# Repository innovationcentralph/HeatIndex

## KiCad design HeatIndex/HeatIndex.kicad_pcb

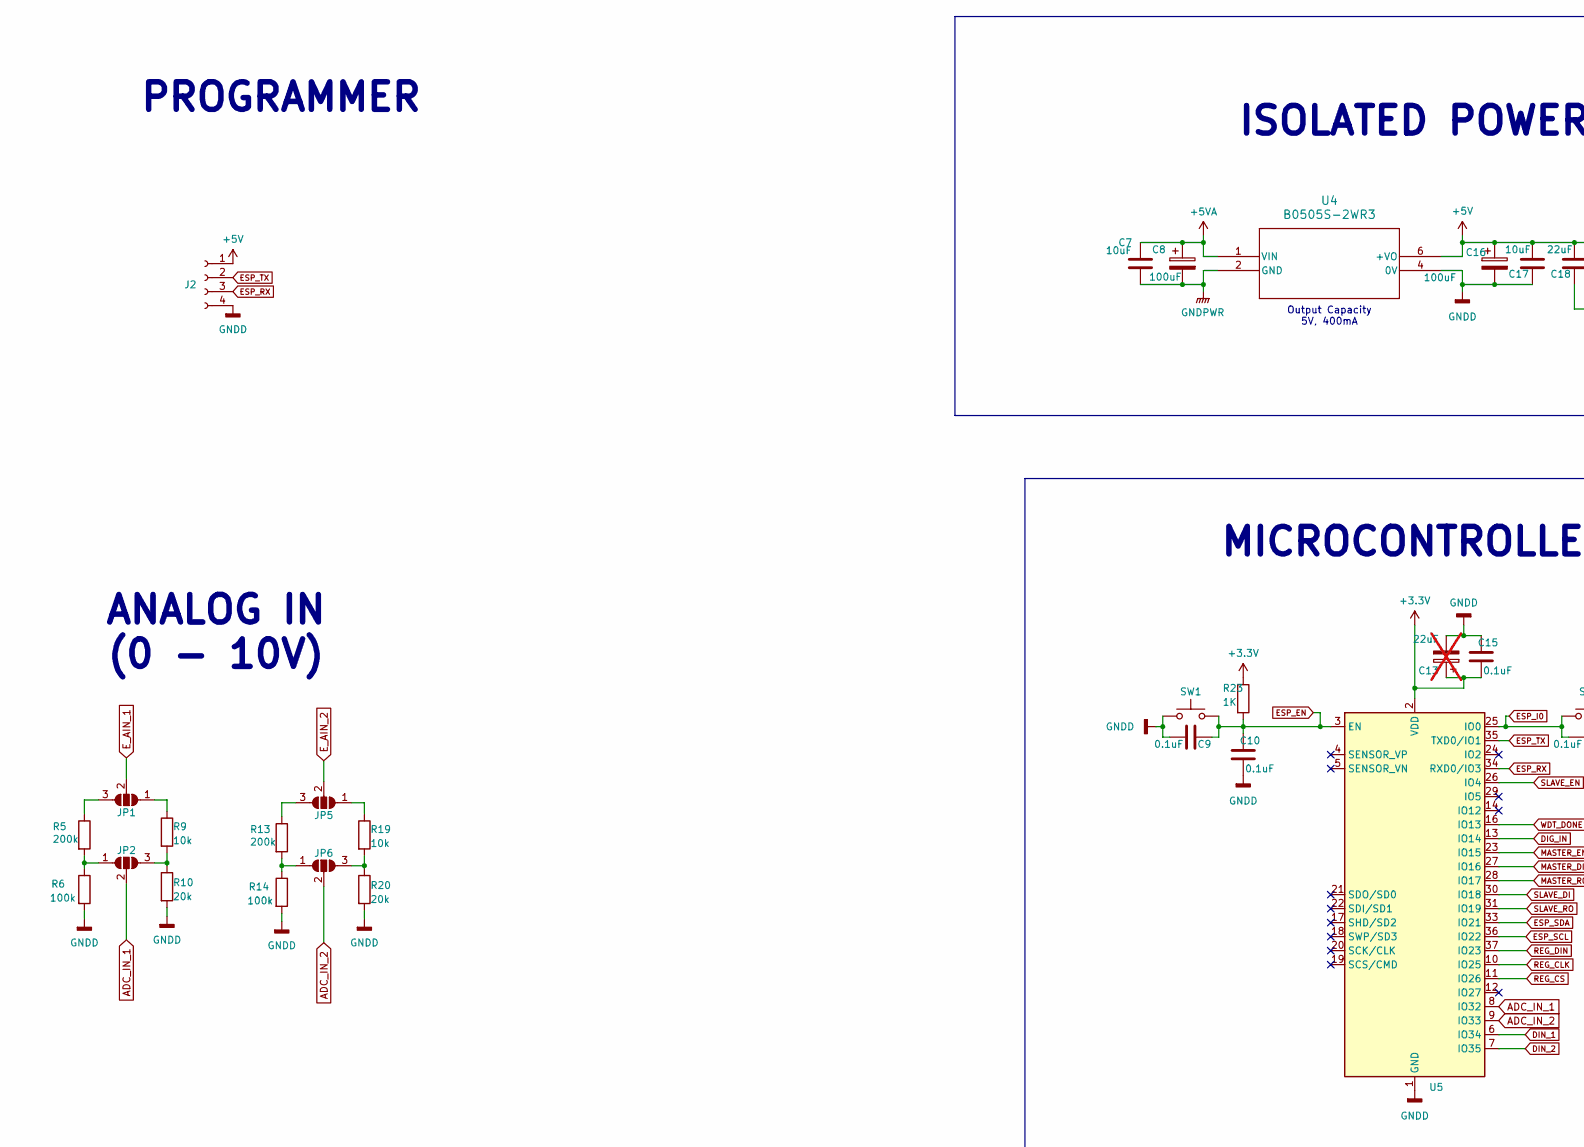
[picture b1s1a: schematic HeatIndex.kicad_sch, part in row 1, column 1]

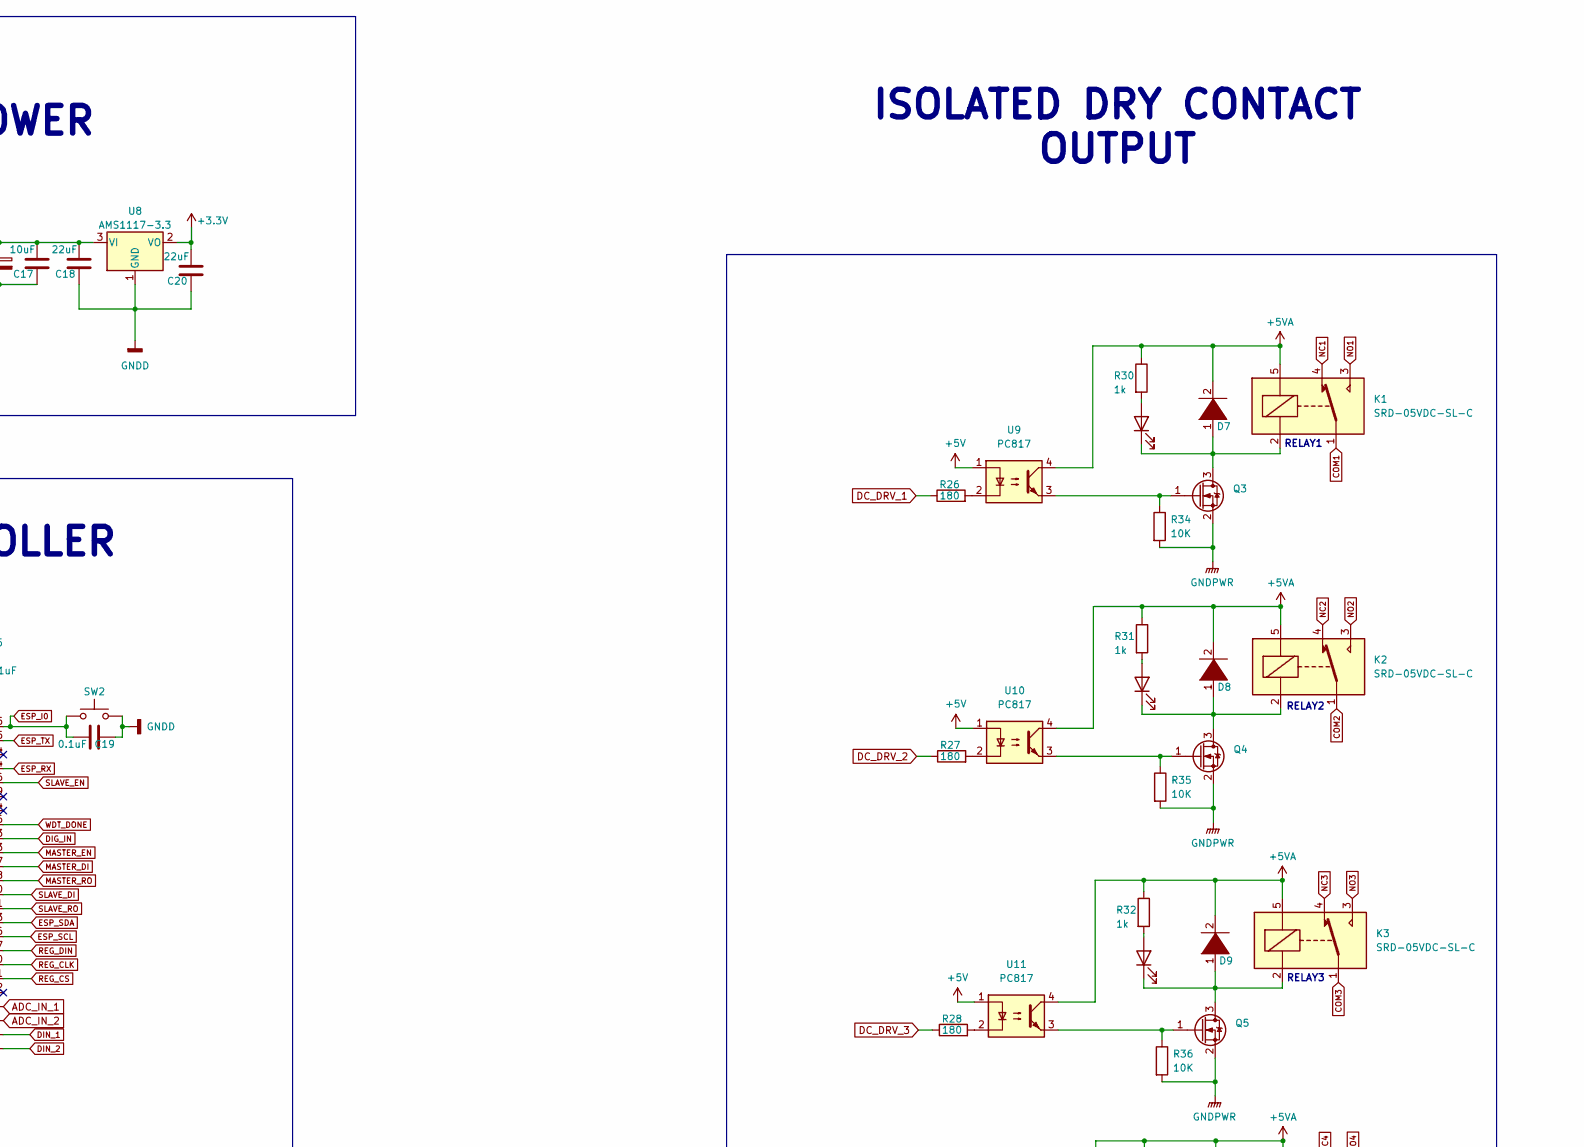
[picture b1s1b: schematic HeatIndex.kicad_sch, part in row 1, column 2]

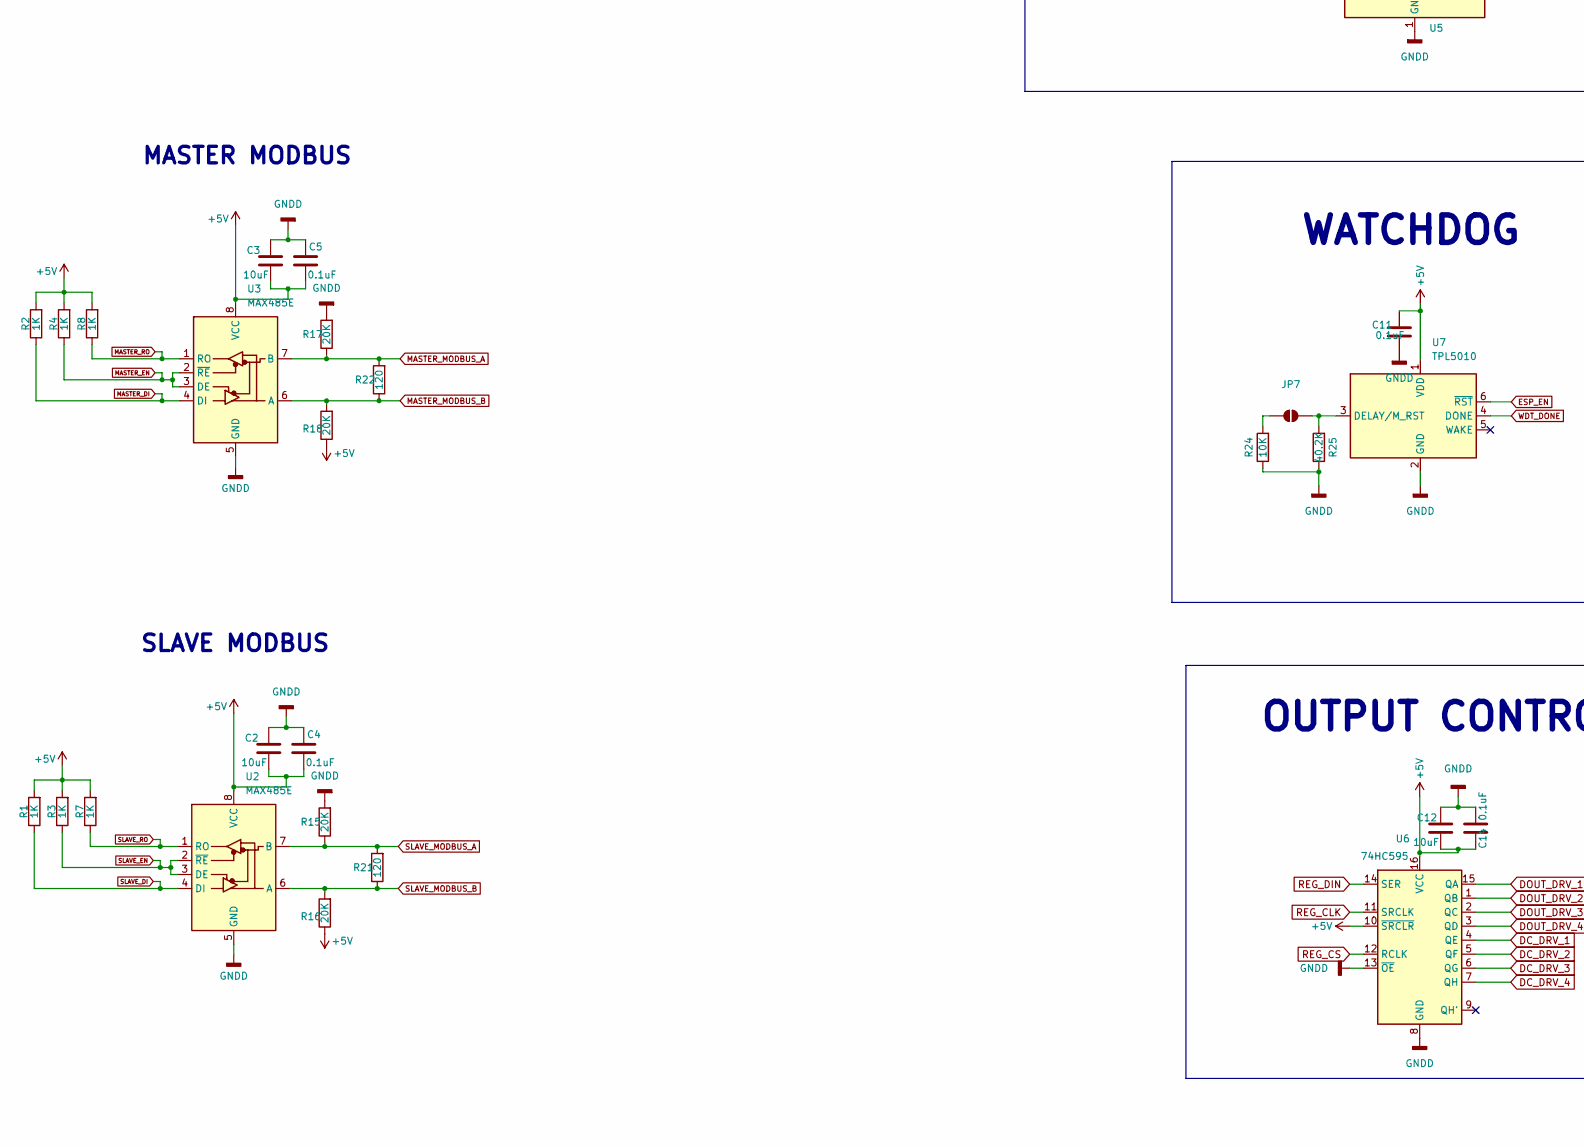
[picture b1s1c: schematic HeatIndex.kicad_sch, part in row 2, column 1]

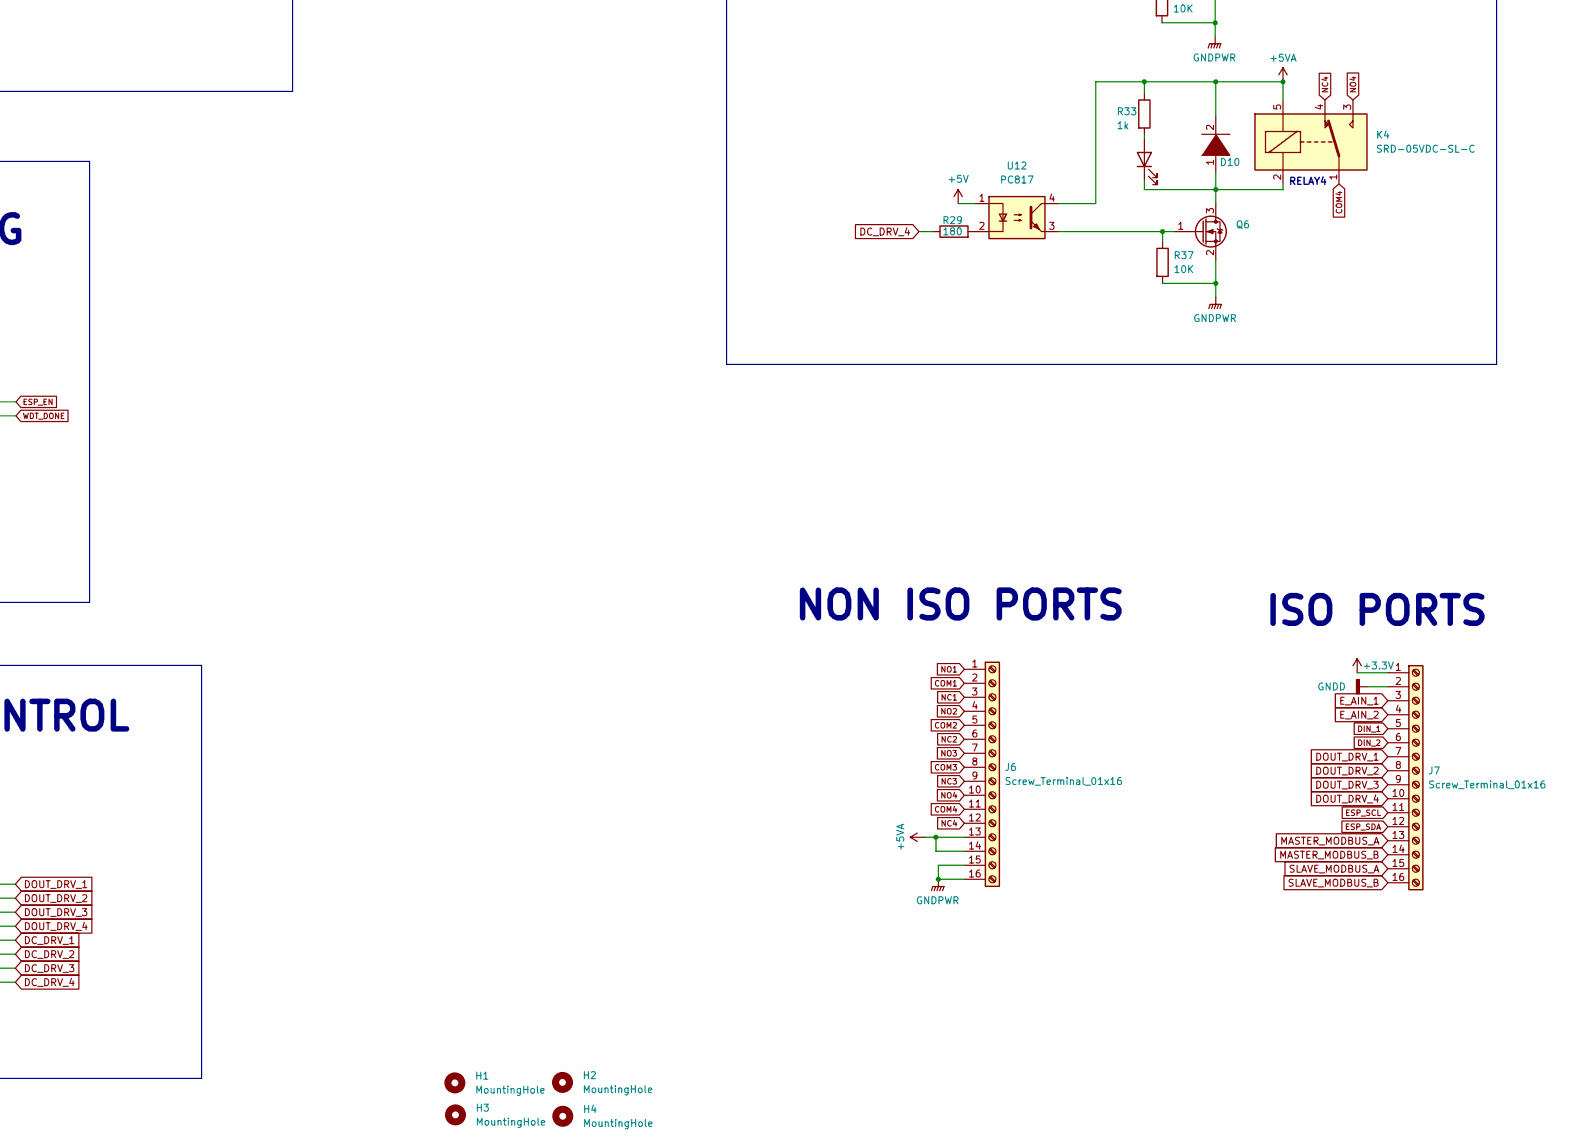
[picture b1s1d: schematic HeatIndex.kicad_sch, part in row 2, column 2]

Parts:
C2, C3, C7, C12, C17: 10uF; C_0805_2012Metric_Pad1.18x1.45mm_HandSolder; LCSC C15850
C4, C5, C9, C10, C11, C14, C15, C19: 0.1uF; C_0603_1608Metric; LCSC C80516
C8, C16: 100uF; C_1210_3225Metric_Pad1.33x2.70mm_HandSolder; LCSC C394395
C13: 22uF; C_0603_1608Metric; LCSC C59461; not fitted
C18, C20: 22uF; C_0603_1608Metric; LCSC C59461
D3, D4, D5, D6: LED; LED_0805_2012Metric_Pad1.15x1.40mm_HandSolder; LCSC C2297
D7, D8, D9, D10: 1N4001; D_SOD-123F; LCSC C2892326
H1, H2, H3, H4: MountingHole; MountingHole_3.2mm_M3_DIN965_Pad_TopBottom
J2: Conn_01x04_Socket; JST_EH_B4B-EH-A_1x04_P2.50mm_Vertical
J6, J7: Screw_Terminal_01x16; TerminalBlock_Phoenix_MKDS-1,5-16-5.08_1x16_P5.08mm_Horizon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
JP1, JP2, JP5, JP6: SolderJumper_3_Open; SolderJumper-3_P1.3mm_Open_Pad1.0x1.5mm
JP7: SolderJumper_2_Open; SolderJumper-2_P1.3mm_Open_Pad1.0x1.5mm
K1, K2, K3, K4: SRD-05VDC-SL-C; Relay_SPDT_SANYOU_SRD_Series_Form_C; LCSC C35449
Q3, Q4, Q5, Q6: Q_NMOS_Depletion_GSD; SOT-23-3; LCSC C75882
R1, R2, R3, R4, R7, R8, R23: 1K; R_0603_1608Metric_Pad0.98x0.95mm_HandSolder; LCSC C21190
R5, R13: 200k; R_0603_1608Metric_Pad0.98x0.95mm_HandSolder; LCSC C95331
R6, R14: 100k; R_0603_1608Metric_Pad0.98x0.95mm_HandSolder; LCSC C14675
R9, R19: 10k; R_0603_1608Metric_Pad0.98x0.95mm_HandSolder; LCSC C25804
R10, R20: 20k; R_0603_1608Metric_Pad0.98x0.95mm_HandSolder; LCSC C2907011
R15, R16, R17, R18: 20K; R_0805_2012Metric_Pad1.20x1.40mm_HandSolder; LCSC C4328
R21, R22: 120; R_0805_2012Metric_Pad1.20x1.40mm_HandSolder; LCSC C114245
R24, R34, R35, R36, R37: 10K; R_0603_1608Metric_Pad0.98x0.95mm_HandSolder; LCSC C25804
R25: 40.2K; R_0603_1608Metric_Pad0.98x0.95mm_HandSolder; LCSC C12447
R26, R27, R28, R29: 180; R_0603_1608Metric_Pad0.98x0.95mm_HandSolder; LCSC C25210
R30, R31, R32, R33: 1k; R_0603_1608Metric_Pad0.98x0.95mm_HandSolder; LCSC C21190
SW1, SW2: SW_Push; SW_SPST_CK_RS282G05A3; LCSC C2689642
U2, U3: MAX485E; SOP-8_3.9x4.9mm_P1.27mm; LCSC C481667
U4: B0505S-2WR3; B_S-2WR2_MNS; LCSC C5369473
U5: ESP32-WROOM-32; LCSC C529577
U6: 74HC595; SOIC-16_3.9x9.9mm_P1.27mm; LCSC C5947
U7: TPL5010; SOT-23-6; LCSC C473912
U8: AMS1117-3.3; SOT-223-3_TabPin2; LCSC C6186
U9, U10, U11, U12: PC817; APC-817xx-SL_AMB; LCSC C66405

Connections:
+3.3V: C13.1, C15.1, C20.2, J7.1, R23.1, U5.2 (VDD), U8.2 (VO)
+5V: C2.2, C3.2, C4.1, C5.1, C11.1, C12.2, C14.2, C16.1, C17.2, C18.2, J2.1, R1.2, R2.2, R3.2, R4.2, R7.2, R8.2, R16.1, R18.1, U2.8 (VCC), U3.8 (VCC), U4.6 (+VO), U6.10 (~SRCLR), U6.16 (VCC), U7.1 (VDD), U8.3 (VI), U9.1, U10.1, U11.1, U12.1
+5VA: C7.2, C8.1, D7.2 (A), D8.2 (A), D9.2 (A), D10.2 (A), J6.13, J6.14, K1.5, K2.5, K3.5, K4.5, R30.1, R31.1, R32.1, R33.1, U4.1 (VIN), U9.4, U10.4, U11.4, U12.4
ADC_IN_1: JP2.2 (C), U5.8 (IO32)
ADC_IN_2: JP6.2 (C), U5.9 (IO33)
COM1: J6.2, K1.1
COM2: J6.5, K2.1
COM3: J6.8, K3.1
COM4: J6.11, K4.1
DC_DRV_1: R26.1, U6.4 (QE)
DC_DRV_2: R27.1, U6.5 (QF)
DC_DRV_3: R28.1, U6.6 (QG)
DC_DRV_4: R29.1, U6.7 (QH)
DIG_IN: U5.13 (IO14)
DIN_1: J7.5, U5.6 (IO34)
DIN_2: J7.6, U5.7 (IO35)
DOUT_DRV_1: J7.7, U6.15 (QA)
DOUT_DRV_2: J7.8, U6.1 (QB)
DOUT_DRV_3: J7.9, U6.2 (QC)
DOUT_DRV_4: J7.10, U6.3 (QD)
ESP_EN: C9.2, C10.2, R23.2, SW1.2, U5.3 (EN), U7.6 (~RST)
ESP_I0: C19.1, SW2.1, U5.25 (IO0)
ESP_RX: J2.3, U5.34 (RXD0/IO3)
ESP_SCL: J7.11, U5.36 (IO22)
ESP_SDA: J7.12, U5.33 (IO21)
ESP_TX: J2.2, U5.35 (TXD0/IO1)
E_AIN_1: J7.3, JP1.2 (C)
E_AIN_2: J7.4, JP5.2 (C)
GNDD: C2.1, C3.1, C4.2, C5.2, C9.1, C10.1, C11.2, C12.1, C13.2, C14.1, C15.2, C16.2, C17.1, C18.1, C19.2, C20.1, J2.4, J7.2, R6.2, R10.2, R14.2, R15.2, R17.2, R20.2, R24.1, R25.1, SW1.1, SW2.2, U2.5 (GND), U3.5 (GND), U4.4 (0V), U5.1 (GND), U5.15 (GND), U5.38 (GND), U5.39 (GND), U6.8 (GND), U6.13 (~OE), U7.2 (GND), U8.1 (GND)
GNDPWR: C7.1, C8.2, J6.15, J6.16, Q3.2 (S), Q4.2 (S), Q5.2 (S), Q6.2 (S), R34.2, R35.2, R36.2, R37.2, U4.2 (GND)
MASTER_DI: R2.1, U3.4 (DI), U5.27 (IO16)
MASTER_EN: R4.1, U3.2 (~RE), U3.3 (DE), U5.23 (IO15)
MASTER_MODBUS_A: J7.13, R17.1, R22.2, U3.7 (B)
MASTER_MODBUS_B: J7.14, R18.2, R22.1, U3.6 (A)
MASTER_RO: R8.1, U3.1 (RO), U5.28 (IO17)
NC1: J6.3, K1.4
NC2: J6.6, K2.4
NC3: J6.9, K3.4
NC4: J6.12, K4.4
NO1: J6.1, K1.3
NO2: J6.4, K2.3
NO3: J6.7, K3.3
NO4: J6.10, K4.3
unnamed: D3.2 (A), R30.2
unnamed: D3.1 (K), D7.1 (K), K1.2, Q3.3 (D)
unnamed: D4.2 (A), R31.2
unnamed: D4.1 (K), D8.1 (K), K2.2, Q4.3 (D)
unnamed: D5.2 (A), R32.2
unnamed: D5.1 (K), D9.1 (K), K3.2, Q5.3 (D)
unnamed: D6.2 (A), R33.2
unnamed: D6.1 (K), D10.1 (K), K4.2, Q6.3 (D)
unnamed: JP1.1 (A), R9.1
unnamed: JP1.3 (B), R5.1
unnamed: JP2.1 (A), R5.2, R6.1
unnamed: JP2.3 (B), R9.2, R10.1
unnamed: JP5.1 (A), R19.1
unnamed: JP5.3 (B), R13.1
unnamed: JP6.1 (A), R13.2, R14.1
unnamed: JP6.3 (B), R19.2, R20.1
unnamed: JP7.1 (A), R24.2
unnamed: JP7.2 (B), R25.2, U7.3 (DELAY/M_RST)
unnamed: Q3.1 (G), R34.1, U9.3
unnamed: Q4.1 (G), R35.1, U10.3
unnamed: Q5.1 (G), R36.1, U11.3
unnamed: Q6.1 (G), R37.1, U12.3
unnamed: R26.2, U9.2
unnamed: R27.2, U10.2
unnamed: R28.2, U11.2
unnamed: R29.2, U12.2
REG_CLK: U5.10 (IO25), U6.11 (SRCLK)
REG_CS: U5.11 (IO26), U6.12 (RCLK)
REG_DIN: U5.37 (IO23), U6.14 (SER)
SLAVE_DI: R1.1, U2.4 (DI), U5.30 (IO18)
SLAVE_EN: R3.1, U2.2 (~RE), U2.3 (DE), U5.26 (IO4)
SLAVE_MODBUS_A: J7.15, R15.1, R21.2, U2.7 (B)
SLAVE_MODBUS_B: J7.16, R16.2, R21.1, U2.6 (A)
SLAVE_RO: R7.1, U2.1 (RO), U5.31 (IO19)
WDT_DONE: U5.16 (IO13), U7.4 (DONE)

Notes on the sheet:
RELAY1
Output Capacity 5V, 400mA
WATCHDOG
RELAY4
ISOLATED DRY CONTACT OUTPUT
MASTER MODBUS
SLAVE MODBUS
ISOLATED POWER
RELAY3
PROGRAMMER
ISO PORTS
MICROCONTROLLER
NON ISO PORTS
ANALOG IN (0 - 10V)
OUTPUT CONTROL
RELAY2

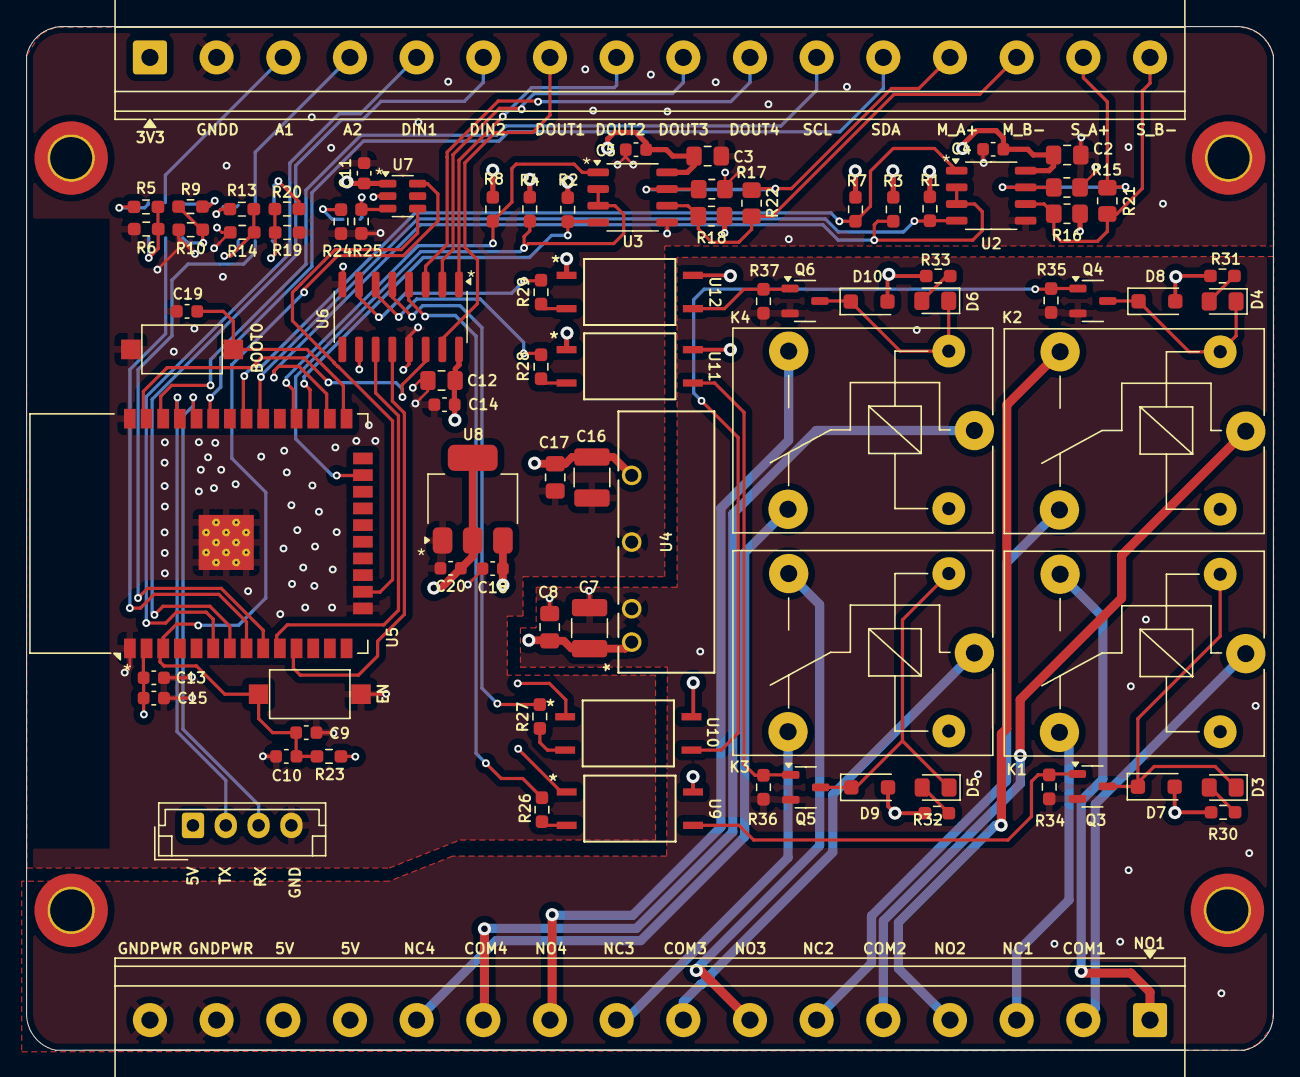
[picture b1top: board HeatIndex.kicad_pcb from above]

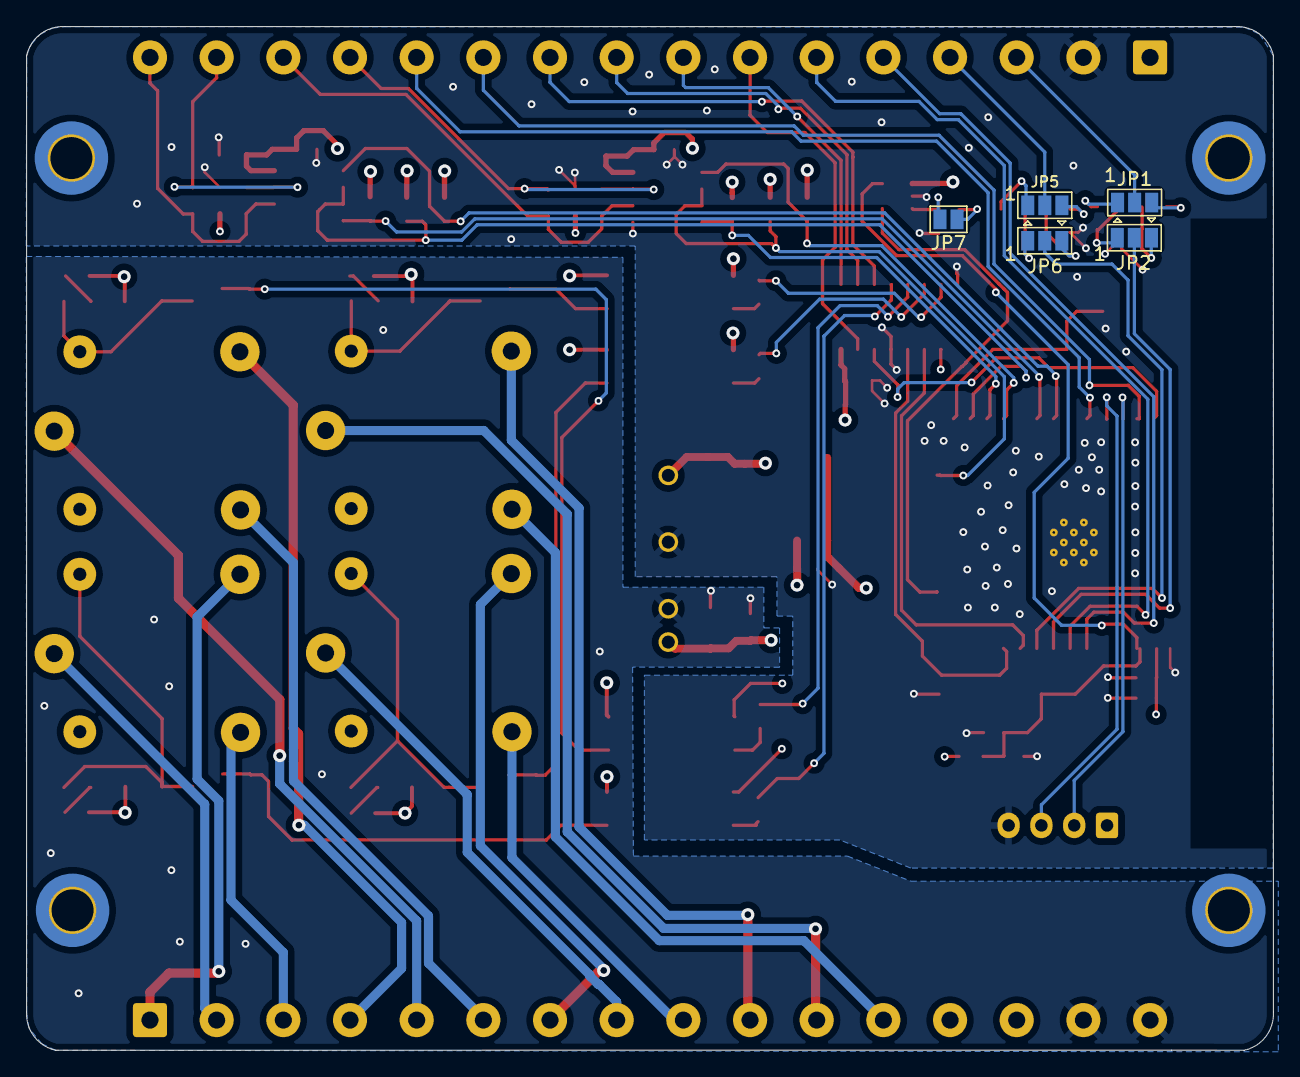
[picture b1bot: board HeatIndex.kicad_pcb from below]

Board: 4 copper layers, 95.0 x 78.0 mm, 94 parts (5 on the bottom side), 77 nets.

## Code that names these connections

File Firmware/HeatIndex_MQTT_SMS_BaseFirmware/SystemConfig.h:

#ifndef SYSTEM_CONFIG_H
#define SYSTEM_CONFIG_H

#include <Arduino.h>
#include "NetworkMqttManager.h"
//==============================================================================
//                              DEBUG FLAGS
//==============================================================================
// Uncomment to enable serial debug output for each subsystem
 #define DEBUG_WIFI
 #define DEBUG_MQTT
 #define DEBUG_SENSOR
 #define DEBUG_TH
 #define DEBUG_CONTACTS
 #define DEBUG_SMS


//==============================================================================
//                               HARDWARE PINS
//==============================================================================


// Master enable / data lines (e.g., for GSM or other radio)
#define MASTER_RO 26  // Master Read Only line
#define MASTER_DI 25  // Master Data In line
#define MASTER_EN 27  // Master Enable line

#define GSM_PWR 4

// LEDs
#define NETWORK_INDICATOR 12     // Server Connectivity LED
#define ACTIVE_INDICATOR 13  // IDLE Indicator LED
#define LED_ON HIGH
#define LED_OFF LOW

//==============================================================================
//                             STRUCTURES
//==============================================================================
typedef struct {
  char mqttServer[64];
  char mqttUser[32];
  char mqttPassword[32];
  int mqttPort;
} MQTTConfig_t;

typedef struct {
  char ssid[32];
  char password[64];
} WiFiCreds_t;

typedef struct{
  int normal;
  int warning;
  int alert;
  int critical;
} Thresholds_t;

typedef struct{
  bool green;
  bool blue;
  bool orange;
  bool red;
} TowerLight_t;

enum TowerLightState {
  STATE_GREEN,
  STATE_BLUE,
  STATE_ORANGE,
  STATE_RED,
  STATE_INIT
};

#define DEFAUL_NETWORK_MODE GSM_ONLY
//==============================================================================
//                             EEPROM SETTINGS
//==============================================================================
// Total EEPROM size (bytes)
#define EEPROM_SIZE 1024

#define DEVICE_ESN_MAX_LEN 32
#define SEND_INTERVAL_SIZE  sizeof(uint32_t)
#define MQTT_CONFIG_SIZE    sizeof(MQTTConfig_t)
#define WIFI_CREDS_SIZE     sizeof(WiFiCreds_t)
#define NETWORK_MODE_SIZE   sizeof(uint8_t)

// Contacts storage
#define MAX_CONTACTS        35
#define CONTACT_MAX_LEN     16         // "+639..." up to 15 chars + NUL
#define CONTACTS_BLOCK_SIZE (1 + (MAX_CONTACTS * CONTACT_MAX_LEN)) // count + data

// ---- Thresholds block (4 x int16 + 1 magic) ----
#define THRESHOLDS_COUNT        4
#define THRESHOLD_FIELD_SIZE    sizeof(int16_t)   // store compactly
#define THRESHOLDS_BLOCK_SIZE   (1 + THRESHOLDS_COUNT * THRESHOLD_FIELD_SIZE) // magic + 4x int16


// Addresses within EEPROM
#define EEPROM_ESN_ADDR               0  // Start address for storing ESN
#define EEPROM_SEND_INTERVAL_ADDR    (EEPROM_ESN_ADDR + DEVICE_ESN_MAX_LEN)
#define EEPROM_MQTT_CONFIG_ADDR      (EEPROM_SEND_INTERVAL_ADDR + SEND_INTERVAL_SIZE) + 10
#define EEPROM_WIFI_CRED_ADDR        (EEPROM_MQTT_CONFIG_ADDR + MQTT_CONFIG_SIZE)
#define EEPROM_NETWORK_MODE_ADDR     (EEPROM_WIFI_CRED_ADDR + WIFI_CREDS_SIZE) 
#define EEPROM_CONTACTS_ADDR         (EEPROM_NETWORK_MODE_ADDR + NETWORK_MODE_SIZE)
#define EEPROM_THRESHOLDS_ADDR        (EEPROM_CONTACTS_ADDR + CONTACTS_BLOCK_SIZE)


#define EEPROM_RESERVED_ADDR           (EEPROM_THRESHOLDS_ADDR + THRESHOLDS_BLOCK_SIZE)



//==============================================================================
//                           DEVICE IDENTIFIERS
//==============================================================================
// Device Electronic Serial Number


extern char deviceESN[DEVICE_ESN_MAX_LEN];
extern MQTTConfig_t mqttConfig;

//==============================================================================
//                           MQTT CONFIGURATION
//==============================================================================
// Configurable MQTT parameters
extern MQTTConfig_t mqttConfig;
extern char deviceESN[DEVICE_ESN_MAX_LEN];

extern Thresholds_t thresholds;
extern TowerLight_t towerLights;

#define TH_HYSTERESIS 0.5

extern String willTopic;
extern String willMessage;
extern String initTopic;
extern String intervalConfig;
extern String mqttConfiguration;

extern String topicPing;
extern String topicPingResp;

extern String topicSensorData;

extern String topicRequestThreshold;
extern String topicThresholds;

extern String topicRequestContacts;
extern String topicContacts;

extern String topicRequestDateTime;
extern String topicGetDateTime;

extern String currentDateTime; 

extern uint32_t hbInterval;

// Wi-Fi credentials
extern const char* wifiSSID;
extern const char* wifiPass;

extern const char* topicInit;


// Timeout for detecting broker disconnect (milliseconds)
#define MQTT_DISCONNECT_TIMEOUT_MS 300000

//==============================================================================
//                         FUNCTION PROTOTYPES
//==============================================================================
// Load and save ESN from EEPROM into deviceESN[]
void loadDeviceESNFromEEPROM(void);
void saveDeviceESNToEEPROM(const char* esn);

// Load and save MQTT Parameters from EEPROM
void loadMQTTConfigFromEEPROM();
void saveMQTTConfigToEEPROM(const MQTTConfig_t& config);

// Load and save heartbeat interval from EEPROM
uint32_t loadHeartbeatInterval();
void saveHeartbeatInterval(uint32_t interval);

// Load dynamic MQTT topics derived from Device ESN
void initializeDynamicTopics();

// Load and Save WiFi Credentials
void saveWiFiCredsToEEPROM(const WiFiCreds_t& creds);
WiFiCreds_t loadWiFiCredsFromEEPROM();

void saveNetworkMode(NetworkMode mode);
NetworkMode loadNetworkMode();

uint32_t readSendIntervalFromEEPROM();
void writeSendIntervalToEEPROM(uint32_t interval);

bool saveThresholdsToEEPROM(const Thresholds_t& in);
bool loadThresholdsFromEEPROM(Thresholds_t& out);


#endif  // SYSTEM_CONFIG_H

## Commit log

2025-08-19 -heat index lcsc checking
2025-09-29 -push firmware
2025-10-16 Update Firmware File Final
2025-10-16 Documents
2025-10-29 Modifie SMS Blasting Logic and Added Binary Files
2025-10-31 Modified firmware to have getDateTime redundancy thru parallel RTOS Task
